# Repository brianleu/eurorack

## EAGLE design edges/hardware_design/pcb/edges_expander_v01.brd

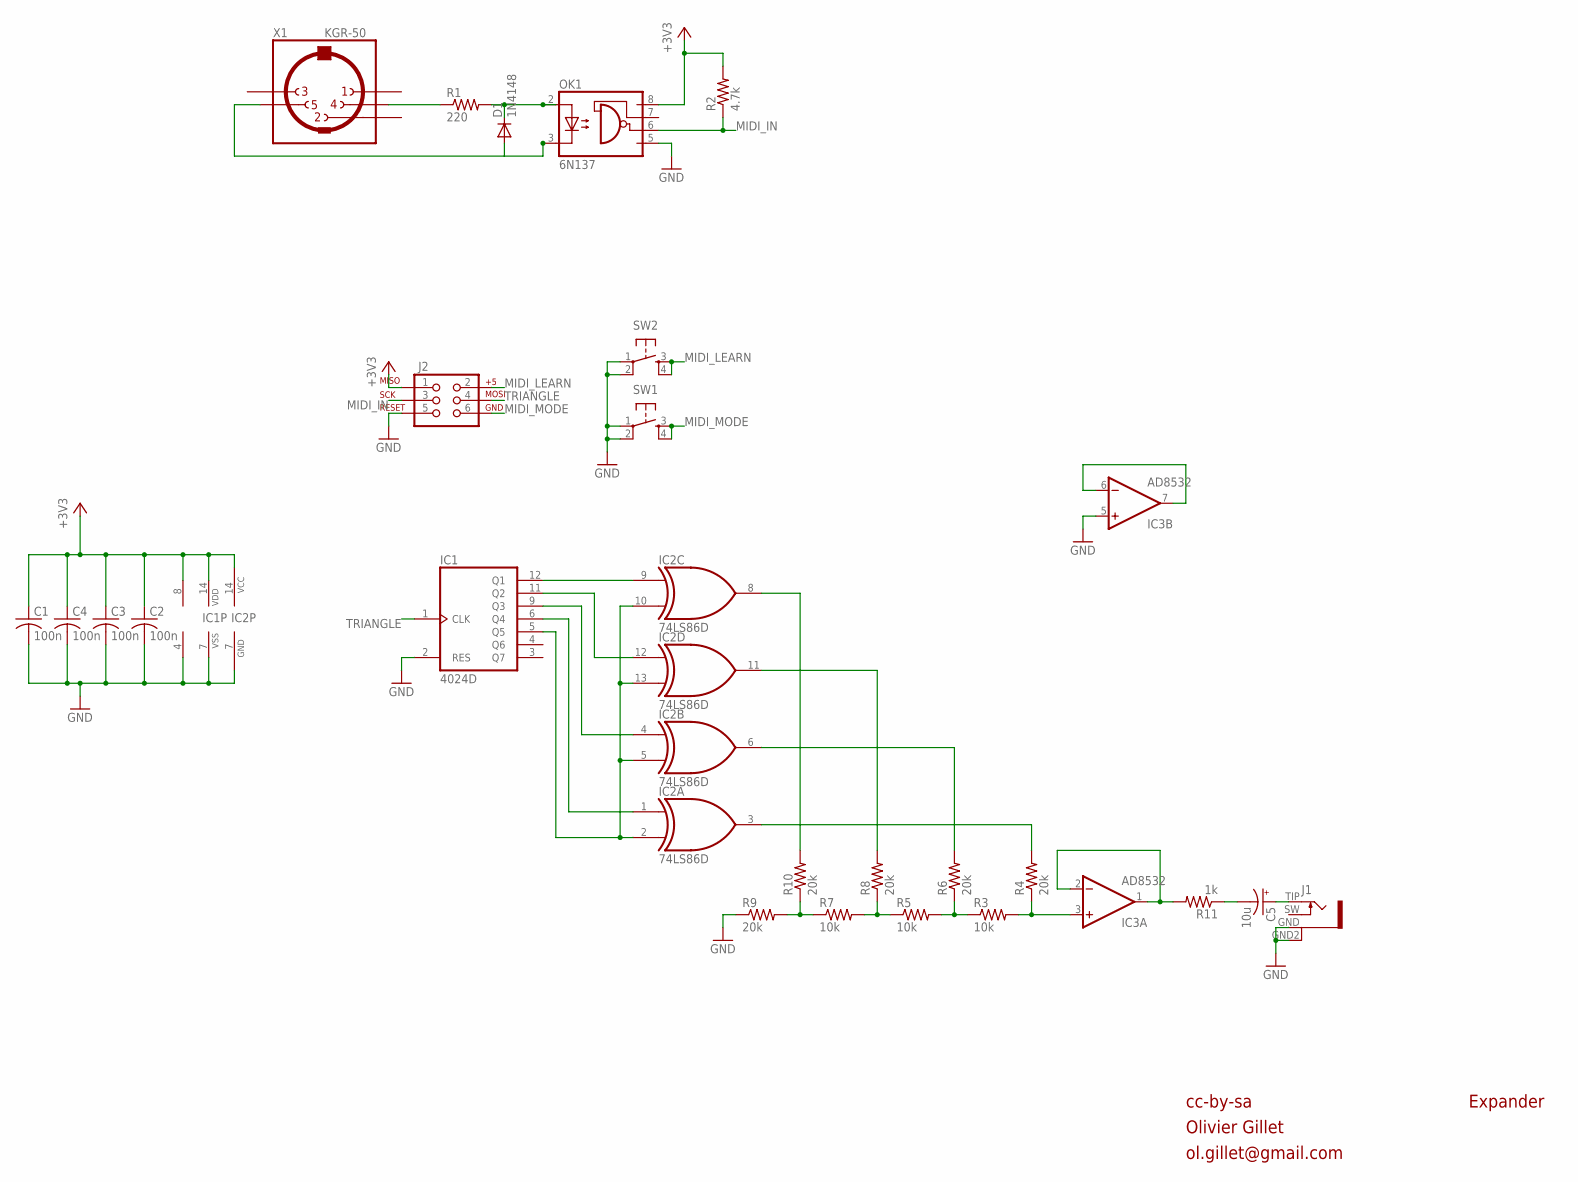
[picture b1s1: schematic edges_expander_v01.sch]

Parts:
C1, C2, C3, C4: 100n; C0603
C5: 10u; PANASONIC_B
D1: 1N4148; SOD323-W
IC1: 4024D; SO14
IC2: 74LS86D; SO14
IC3: AD8532; SO08
J1: PJ301WQP; WQP_PJ_301BM
J2: AVR_SPI_PRG_6PTH; 2X3
OK1: 6N137; DIL8-SMD
R1: 220; R0603
R2: 4.7k; R0603
R3, R5, R7: 10k; R0603
R4, R6, R8, R9, R10: 20k; R0603
R11: 1k; R0603
SW1, SW2: TAC_SWITCHPTH; TACTILE-PTH
X1: KGR-50

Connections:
+3V3_EXP: C1.1, C2.1, C3.1, C4.1, IC1.14 (VDD), IC2.14 (VCC), IC3.8 (V+), J2.1, OK1.8 (VCC), R2.2
GND: C1.2, C2.2, C3.2, C4.2, IC1.2 (RES), IC1.7 (VSS), IC2.7 (GND), IC3.4 (V-), IC3.5 (+IN), J1.GND (1), J1.GND2 (4), J2.5, OK1.5 (GND), R9.1, SW1.1, SW1.2, SW2.1, SW2.2
MIDI_IN: J2.3, OK1.6 (VO), R2.1
MIDI_IN4: R1.1, X1.P$4 (4)
MIDI_IN5: D1.A, OK1.3 (C), X1.P$5 (5)
MIDI_LEARN: J2.2, SW2.3, SW2.4
MIDI_MODE: J2.6, SW1.3, SW1.4
unnamed: IC2.3 (O), R4.2
unnamed: IC2.6 (O), R6.2
unnamed: IC2.11 (O), R8.2
unnamed: IC2.8 (O), R10.2
unnamed: D1.C, OK1.2 (A), R1.2
unnamed: IC1.5 (Q5), IC2.2 (I1), IC2.5 (I1), IC2.10 (I1), IC2.13 (I1)
unnamed: IC1.9 (Q3), IC2.4 (I0)
unnamed: IC1.11 (Q2), IC2.12 (I0)
unnamed: IC1.12 (Q1), IC2.9 (I0)
unnamed: IC3.6 (-IN), IC3.7 (OUT)
unnamed: IC1.6 (Q4), IC2.1 (I0)
unnamed: R7.1, R9.2, R10.1
unnamed: R5.1, R7.2, R8.1
unnamed: R3.1, R5.2, R6.1
unnamed: IC3.3 (+IN), R3.2, R4.1
unnamed: C5.-, R11.1
unnamed: IC3.1 (OUT), IC3.2 (-IN), R11.2
unnamed: C5.+, J1.TIP (2)
TRIANGLE: IC1.1 (CLK), J2.4

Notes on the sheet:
cc-by-sa
Olivier Gillet
ol.gillet@gmail.com
Expander

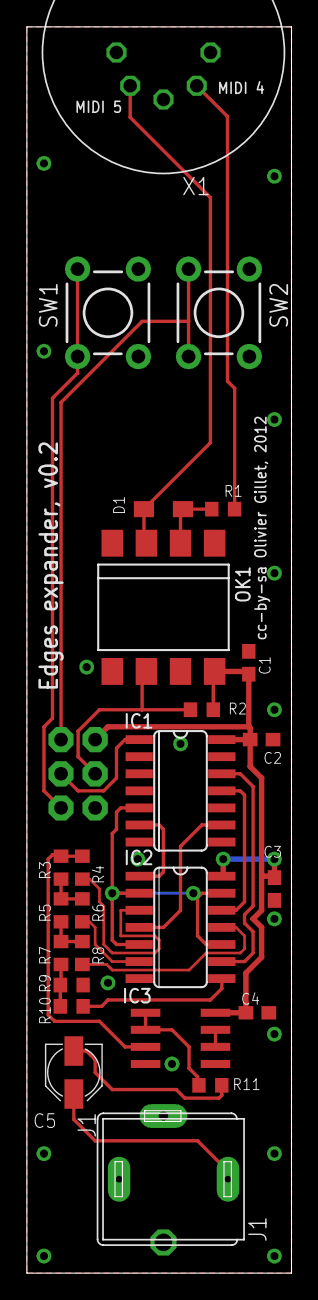
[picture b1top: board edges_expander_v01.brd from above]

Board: 2 copper layers, 19.7 x 92.7 mm, 27 parts (1 on the bottom side), 26 nets.

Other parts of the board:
U$2: EURORACK_TEMPLATE

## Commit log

2018-10-20 First pass at adding a through hole DIN connector to Edges expander
2018-10-20 Add expander BOM and panel eagle brd
